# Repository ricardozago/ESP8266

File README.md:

# Guia inicial do ESP8266

O ESP8266 é um microcontrolador com grande capacidade de processamento (80 MHz de processador com 96 KB de RAM para dados), com suporte a redes Wifi. [Seu artigo na Wikipédia](https://en.wikipedia.org/wiki/ESP8266) é um bom ponto de partida para entender melhor. Ele está disponível em vários empacotamentos, onde a versão chamada de ESP-01 pode ser utilizada como um chip para fornecer acesso Wifi para o Arduino (ironicamente possuindo muito mais capacidade de processamento que o próprio Arduino Uno R3). O ESP8266 sozinho pode ser utilizado no lugar do Arduino utilizando a mesma IDE para processamento, no entanto nosso foco aqui é utilizá-lo como um periférico no Arduino.

Pode ser necessário atualizar o Firmware no ESP-01. A versão mais atual (para a versão com 512 KB, 4 Mb de memória ROM, esp8266_nonos_sdk_v2.0.0_16_08_10) pode ser encontrada na pasta do Github ou [aqui](http://espressif.com/en/support/download/sdks-demos). Aparentemente a versão 2.1 não é compatível com a versão de 4 Mb de memória ROM. Os arquivos para atualização do Firmware eagle.flash.bin e eagle.irom0text.bin estarão no arquivo compactado na pasta bin/at/noboot. Também serão utilizados os arquivos esp_init_data_default.bin e blank.bin na pasta /bin. Para facilitar eles estão na pasta [Firmware AT 4 Mb](https://github.com/ricardozago/ESP8266/tree/master/Firmware%20AT%204%20Mb) deste repositório.

Para gravar o firmware podem ser utilizados diversos softwares. Existe uma ferramenta muito rica escrita em Python chamada [esptool.py](https://github.com/espressif/esptool), no entanto usaremos o gravador (flash_download_tools_v3.4.9.2_0), disponível na pasta ou em seu [site oficial](http://www.espressif.com/en/support/download/other-tools). Para o ESP entrar no modo de gravação da imagem é necessário iniciá-lo com a porta GPIO0 aterrada. Também é possível colocar o reset no terra, aterrar o GPIO0, remover o reset do terra e posteriormente o GPIO0.

O [site do Filipeflop](http://blog.filipeflop.com/wireless/upgrade-de-firmware-do-modulo-esp8266.html) demonstra a montagem do circuito necessária. Também existe um projeto de um shield para o Arduino Uno R3 para facilitar a gravação, disponível [nesta pasta](https://github.com/ricardozago/ESP8266/tree/master/ESP-01%20Firmware%20Flasher), uma imagem da placa é mostrada abaixo.

Para realizar o microcontrolador Atmel do Arduino não interferir na gravação do Firmware é necessário enviar um Sketch vazio para o Arduino. Como o padrão:

    void setup() {
      // put your setup code here, to run once:

    }

    void loop() {
      // put your main code here, to run repeatedly:

    }

As configurações do gravador de ROM podem ser as mesmas da imagem abaixo:

# Ainda na interface do gravador

O baudrate padrão do ESP é 115200, pode-se utilizar um software de terminal para comunicação, como o [Termite](https://www.compuphase.com/software_termite.htm). Entre nas configurações do termite e em Transmitted text marque a opção:

    Append CR-LF
    
Esta opção adiciona um retorno de cursor e uma nova linha ao comando, necessário para o ESP entender que você acabou de enviar o comando. Para verificar a comunicação com o terminal envia o comando:

    AT

O ESP deverá responder com:

    OK

O Arduino Uno R3, possui apenas uma porta de comunicação UART, que é conectada do chip FTDI para conversão para USB. O ESP pode ser conectado nessa mesma interface, mas isso acarreta problemas de comunicação e dificuldade de programação, já que você terá 3 sistemas "conversando" em uma interface onde apenas deveriam existir 2 sistemas. Uma solução é utilizar uma biblioteca que transforma um GPIO qualquer do Arquino em porta serial, o que acarreta problemas de comunicação em baud-rates elevados, portanto é necessário dominuir o baudrate da interface UART do ESP. O comando abaixo, em um firmware atualizado faz isso:

    AT+UART_DEF=19200,8,1,0,0
    
Agora você já está pronto para conectar o ESP diretamente no Arduino. Utilize o Shield, cujo projeto está disponível na [pasta](https://github.com/ricardozago/ESP8266/tree/master/Arduino%20Shield).

O Sketch [disponível aqui](https://github.com/ricardozago/ESP8266/tree/master/ESP-Espelho) copia os comandos enviados via terminal para o Arduino para o ESP e vice-versa. Isto permite conversar diretamente com o ESP e enteder melhor o seu funcionamento.

Inicialmente envie o comando:

    AT+GMR

A versão do firmware será exibida, por exemplo:

    AT version:1.3.0.0(Jul 14 2016 18:54:01)
    SDK version:2.0.0(656edbf)
    compile time:Jul 19 2016 18:43:55
    OK

Utilize o comando abaixo para verificar em qual modo de operação o ESP está funcionando.

    AT+CWMODE?

Os possíveis modos de operação são:

1 = Cliente
2 = Ponto de acesso
3 = Cliente + Ponto de acesso

O comando abaixo passa para o modo cliente:

    AT+CWMODE=1
    
É possível fazer uma busca nas redes disponíveis com:

    AT+CWLAP
    
Ele retornará uma lista de redes disponíveis. Por exemplo:

    +CWLAP:(5,"eduroam",-86,"d8:c7:c8:78:19:02",1,6,0)
    +CWLAP:(0,"Unicamp-Configuracao",-64,"d8:c7:c8:78:18:d0",1,15,0)

O comando abaixo se conecta a alguma das redes disponíveis:

    AT+CWJAP="ssid","pass"
    
Mostra o IP:

    AT+CIFSR
    
O abaixo se desconecta:

    AT+CWQAP
    
Lembrando, as configurações são salvas. Quando você desliga e liga o ESP, ele continua com as mesmas configurações anteriores, como o baud rate e a última rede conectada.

[Este tutorial do Filipeflop](http://blog.filipeflop.com/wireless/esp8266-arduino-tutorial.html) é um bom ponto de partida para criação de um simples webserver. Apenas alterei o modo de conexão, onde no Filipeflop é necessário um roteador para realizar a conexão, enquanto no meu o próprio ESP é o roteador e os dispositivos se conectam nele. Minha versão modificada está disponível [aqui](https://github.com/ricardozago/ESP8266/tree/master/Arduino%20%2B%20ESP%20-%20p%C3%A1gina%20WEB/Ler_Portas).

Para [alterar o nome da rede](https://github.com/espressif/ESP8266_AT/wiki/CWSAP) no modo AP utilize o comando:

    AT+CWSAP="nome_da_rede","senha",chl,ecn
    
onde se a ecn  é igual a 0 a criptografia está desabilitada. Caso queira habilitar: WEP (1), WPA-PSK (2), WPA2-PSK (3) e WPA/WPA2-PSK (4). Já chl é o canal que a rede é criada.

[Esta página](http://allaboutee.com/2015/01/02/esp8266-arduino-led-control-from-webpage/) possui um interessante exemplo para atuar utilizando uma página Web com o Arduino+ESP. Também disponível [neste repositório](https://github.com/ricardozago/ESP8266/tree/master/Arduino%20%2B%20ESP%20-%20p%C3%A1gina%20WEB/Atuar_IO).

# Observações

Todos os layouts de placa desta pasta utilizam o software [Kicad](http://kicad-pcb.org/), a placas foram desenvolvida utilizando como modelo o Shield para arduino disponível como exemplo do Kicad.

Seu layout foi feito a pedido do professor [Fabiano Fruett](http://www.dsif.fee.unicamp.br/~fabiano/) para uso em disciplinas na Faculdade de Engenharia Elétrica e de Computação (FEEC) da Unicamp.

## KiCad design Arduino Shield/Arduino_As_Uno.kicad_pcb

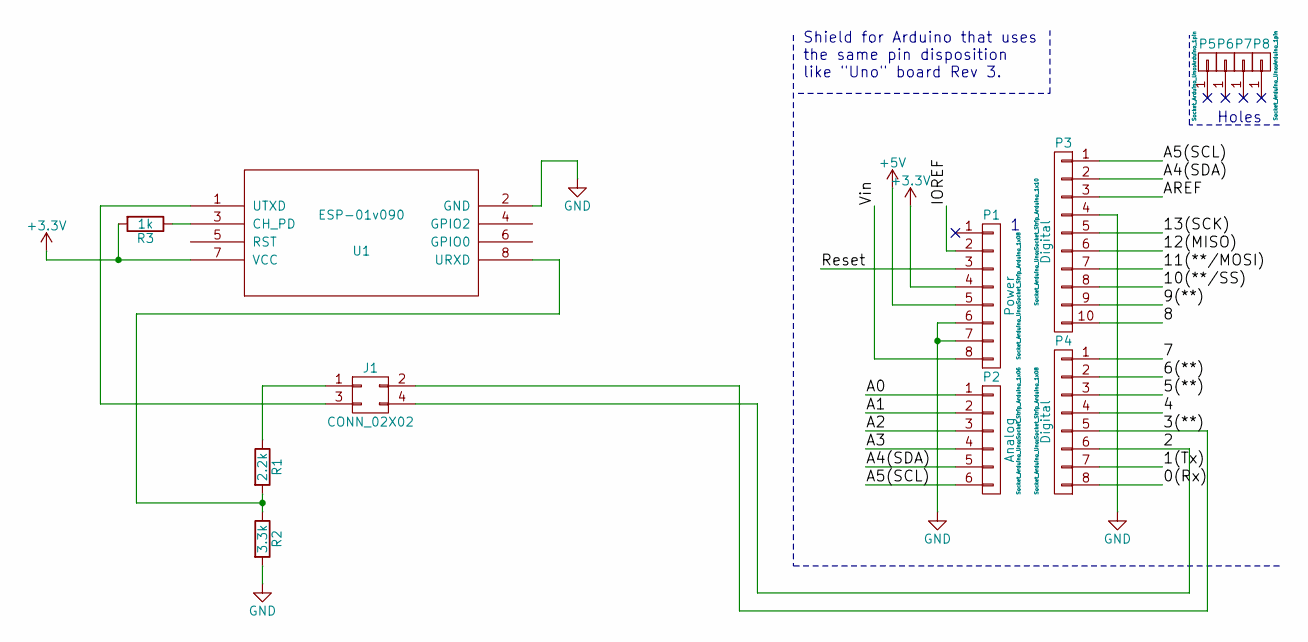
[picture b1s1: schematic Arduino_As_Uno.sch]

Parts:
J1: CONN_02X02; Pin_Header_Straight_2x02_Pitch2.54mm
P1: Power; Socket_Strip_Arduino_1x08
P2: Analog; Socket_Strip_Arduino_1x06
P3: Digital; Socket_Strip_Arduino_1x10
P4: Digital; Socket_Strip_Arduino_1x08
P5, P6, P7, P8: CONN_01X01; Arduino_1pin
R1: 2.2k; R_Axial_DIN0204_L3.6mm_D1.6mm_P7.62mm_Horizontal
R2: 3.3k; R_Axial_DIN0204_L3.6mm_D1.6mm_P7.62mm_Horizontal
R3: 1k; R_Axial_DIN0204_L3.6mm_D1.6mm_P7.62mm_Horizontal
U1: ESP-01v090; ESP-01

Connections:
+3V3: P1.4, R3.2, U1.7 (VCC)
+5V: P1.5
/0(Rx): P4.8
/1(Tx): P4.7
/2: J1.4, P4.6
/3(**): J1.2, P4.5
/4: P4.4
/5(**): P4.3
/6(**): P4.2
/7: P4.1
/8: P3.10
/9(**): P3.9
/10(**/SS): P3.8
/11(**/MOSI): P3.7
/12(MISO): P3.6
/13(SCK): P3.5
/A0: P2.1
/A1: P2.2
/A2: P2.3
/A3: P2.4
/A4(SDA): P2.5, P3.2
/A5(SCL): P2.6, P3.1
/AREF: P3.3
/IOREF: P1.2
/Reset: P1.3
/Vin: P1.8
GND: P1.6, P1.7, P3.4, R2.2, U1.2 (GND)
unnamed: J1.1, R1.1
unnamed: J1.3, U1.1 (UTXD)
unnamed: R1.2, R2.1, U1.8 (URXD)
unnamed: R3.1, U1.3 (CH_PD)

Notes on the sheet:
Holes
Shield for Arduino that uses the same pin disposition like "Uno" board Rev 3.

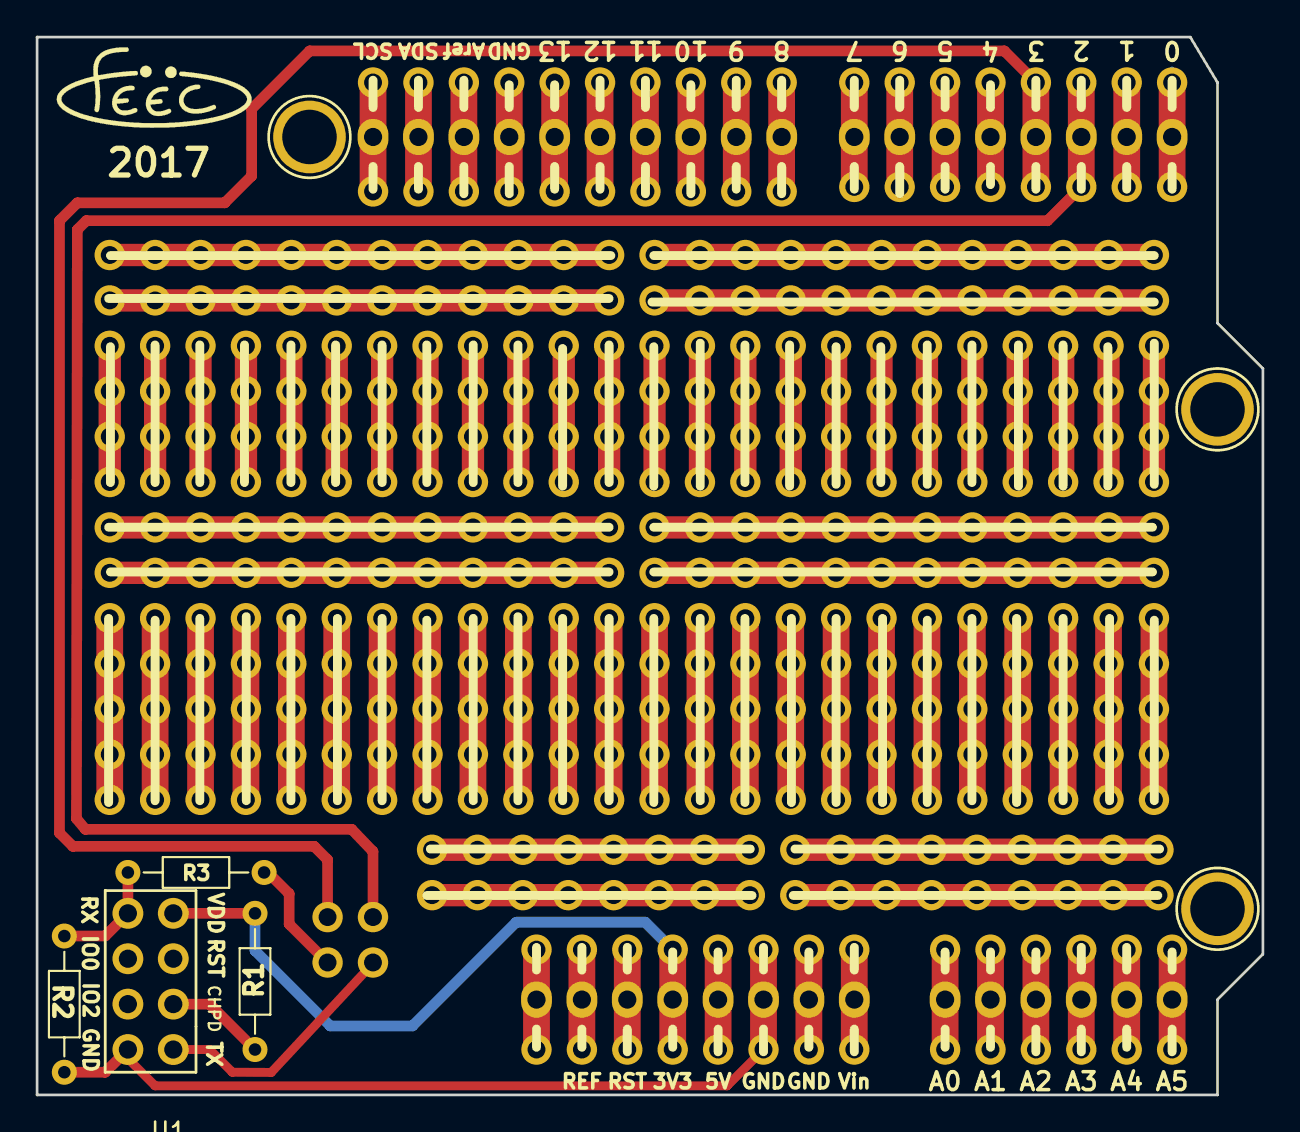
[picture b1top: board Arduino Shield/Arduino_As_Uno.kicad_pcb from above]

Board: 2 copper layers, 68.6 x 59.2 mm, 12 parts (0 on the bottom side), 10 nets.

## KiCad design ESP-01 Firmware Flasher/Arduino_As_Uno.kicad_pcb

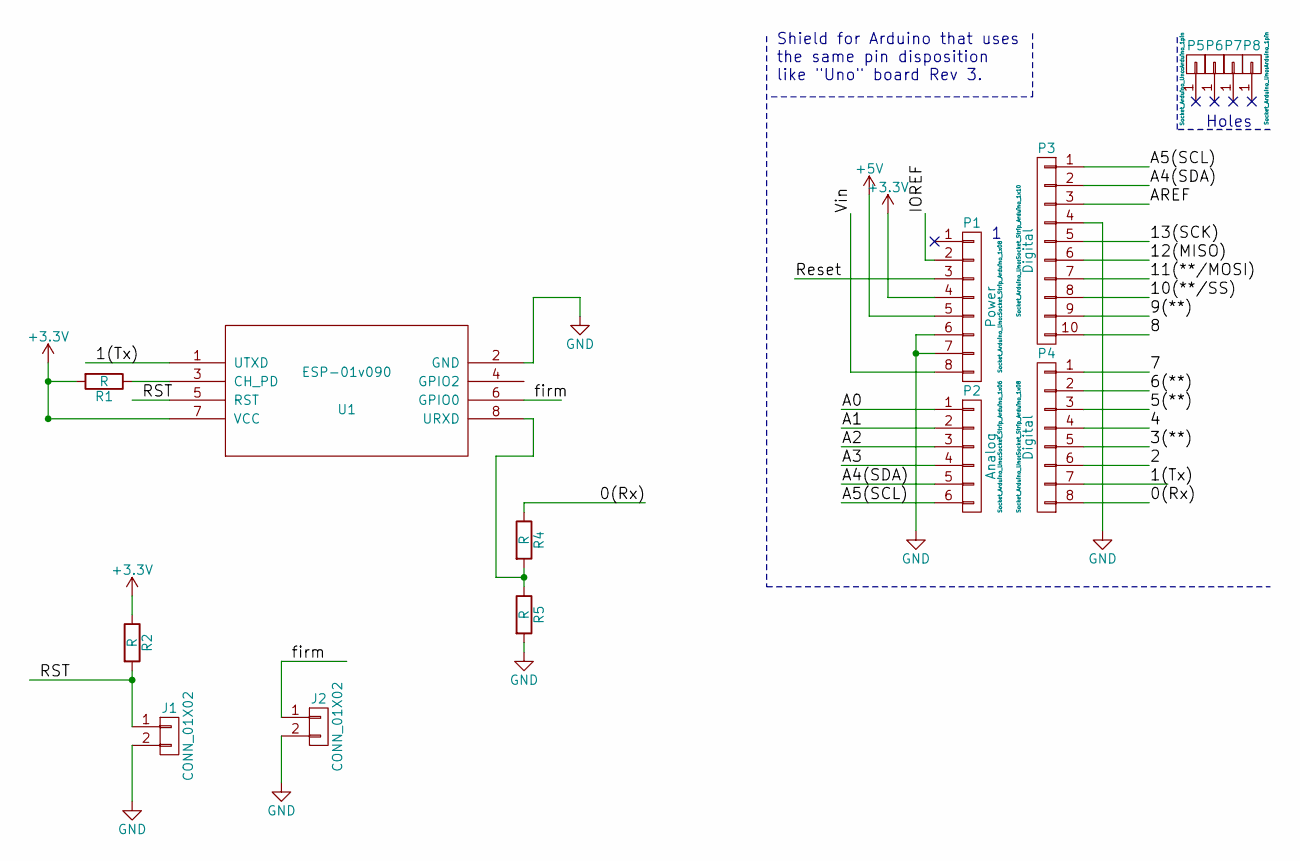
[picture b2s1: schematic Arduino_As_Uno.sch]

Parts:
J1, J2: CONN_01X02; SW_PUSH_6mm_h5mm
P1: Power; Socket_Strip_Arduino_1x08
P2: Analog; Socket_Strip_Arduino_1x06
P3: Digital; Socket_Strip_Arduino_1x10
P4: Digital; Socket_Strip_Arduino_1x08
P5, P6, P7, P8: CONN_01X01; Arduino_1pin
R1, R2, R4, R5: R; R_Axial_DIN0204_L3.6mm_D1.6mm_P7.62mm_Horizontal
U1: ESP-01v090; ESP-01

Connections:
+3V3: P1.4, R1.2, R2.1, U1.7 (VCC)
+5V: P1.5
/0(Rx): P4.8, R4.1
/1(Tx): P4.7, U1.1 (UTXD)
/2: P4.6
/3(**): P4.5
/4: P4.4
/5(**): P4.3
/6(**): P4.2
/7: P4.1
/8: P3.10
/9(**): P3.9
/10(**/SS): P3.8
/11(**/MOSI): P3.7
/12(MISO): P3.6
/13(SCK): P3.5
/A0: P2.1
/A1: P2.2
/A2: P2.3
/A3: P2.4
/A4(SDA): P2.5, P3.2
/A5(SCL): P2.6, P3.1
/AREF: P3.3
/IOREF: P1.2
/RST: J1.1, R2.2, U1.5 (RST)
/Reset: P1.3
/Vin: P1.8
/firm: J2.1, U1.6 (GPIO0)
GND: J1.2, J2.2, P1.6, P1.7, P3.4, R5.2, U1.2 (GND)
unnamed: R1.1, U1.3 (CH_PD)
unnamed: R4.2, R5.1, U1.8 (URXD)

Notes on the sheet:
Holes
Shield for Arduino that uses the same pin disposition like "Uno" board Rev 3.

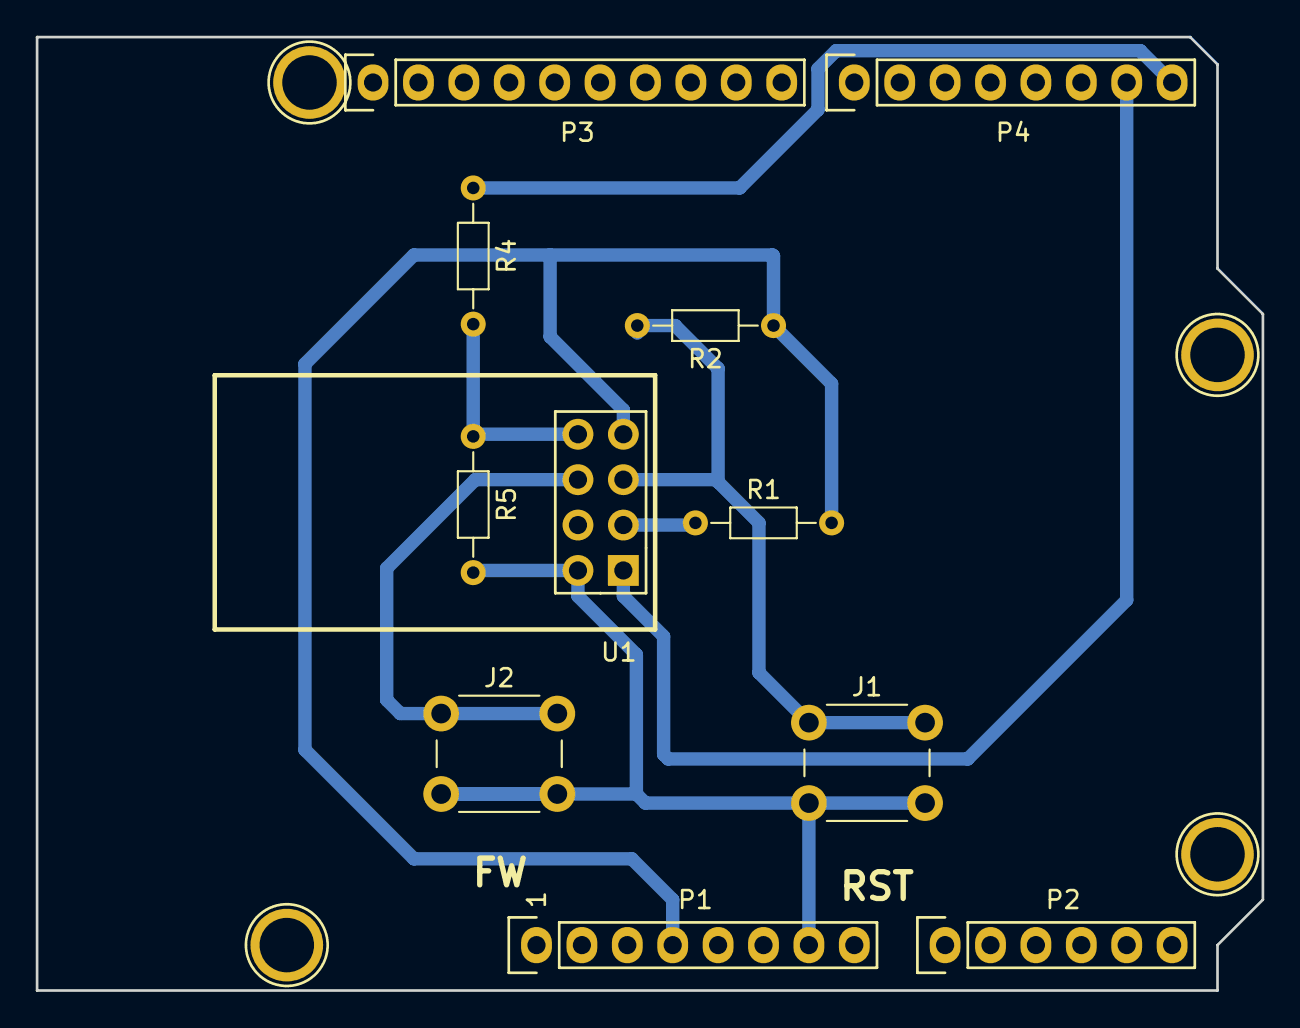
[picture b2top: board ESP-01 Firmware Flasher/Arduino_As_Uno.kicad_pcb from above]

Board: 2 copper layers, 68.6 x 53.3 mm, 15 parts (0 on the bottom side), 10 nets.

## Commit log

2017-08-04 Add Espelho
2017-08-04 Change folder
2017-08-08 Add PCBs layouts
2017-08-08 Update ESP-01 Board
2017-08-08 Just change folder structure
2017-08-09 Update Silkscreen from PCBA
2017-08-09 add firmware files
2017-10-18 Add Webpage Arduino
2017-10-18 Atualiza o README para adicionar a parte de webpage.
2017-10-18 Novas Imagens
2017-10-18 Update images in README
